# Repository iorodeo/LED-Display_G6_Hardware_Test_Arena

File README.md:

## LED-Display\_G6\_Hardware\_Test\_Arena

This repository is part of <https://reiserlab.github.io/Modular-LED-Display/>.
It contains the KiCad design and production files for the G6 panel test arena
hardware.

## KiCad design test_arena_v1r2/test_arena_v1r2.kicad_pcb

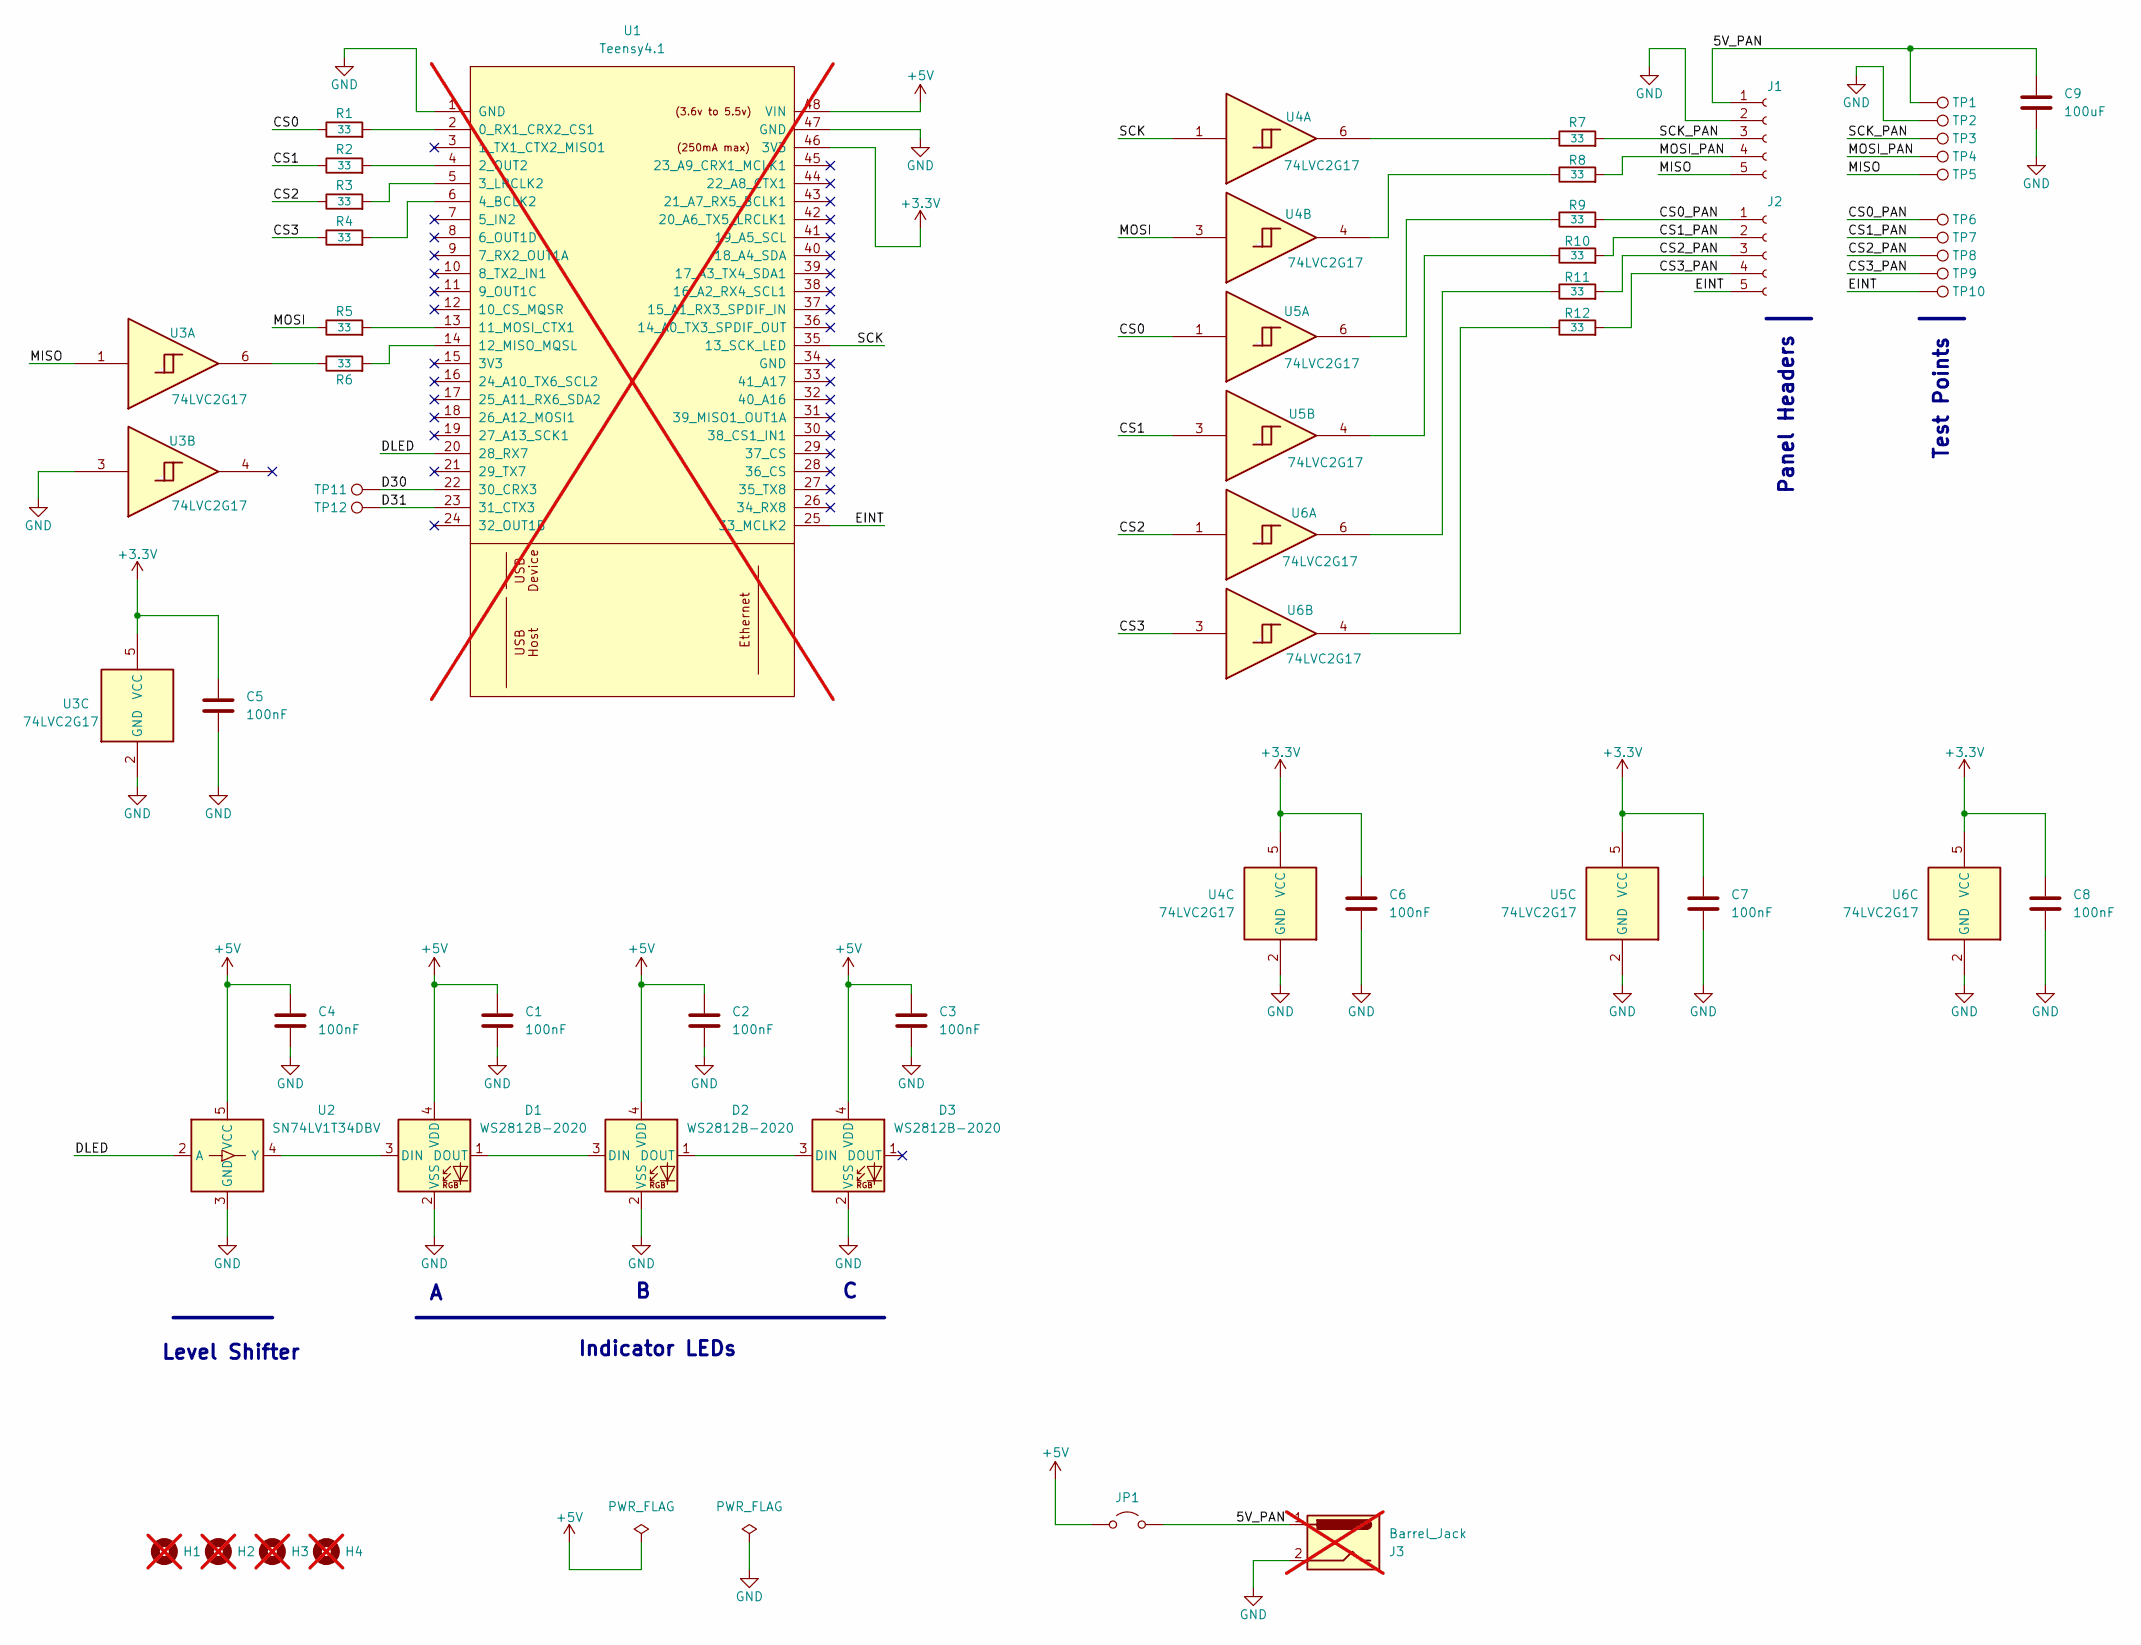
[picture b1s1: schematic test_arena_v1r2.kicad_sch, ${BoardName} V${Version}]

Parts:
C1, C2, C3, C4, C5, C6, C7, C8: 100nF; C_0402_1005Metric; LCSC Part # C1525
C9: 100uF; C_1210_3225Metric; LCSC Part # C84455
D1, D2, D3: WS2812B-2020; LED_WS2812B-2020_PLCC4_2.0x2.0mm; LCSC Part # C965555
H1, H2, H3, H4: MountingHole; MountingHole_3.2mm_M3; not fitted
J1, J2: Conn_01x05_Socket; PinSocket_1x05_P2.54mm_Vertical; LCSC Part # C50950
J3: Barrel_Jack; DCJACK_2PIN_HIGHCURRENT; not fitted
JP1: Jumper_2_Open; PinHeader_1x02_P2.54mm_Vertical; LCSC Part # C492401
R1, R2, R3, R4, R5, R6, R7, R8, R9, R10, R11, R12: 33; R_0402_1005Metric; LCSC Part # C25105
TP1, TP2, TP3, TP4, TP5, TP6, TP7, TP8, TP9, TP10, TP11, TP12: TestPoint; TestPoint_THTPad_D2.0mm_Drill1.0mm; LCSC Part # C238122
U1: Teensy4.1; Teensy41_outer_only; not fitted
U2: SN74LV1T34DBV; SOT-23-5; LCSC Part # C100024
U3, U4, U5, U6: 74LVC2G17; SOT-23-6; LCSC Part # C10429

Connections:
+3.3V: C5.1, C6.1, C7.1, C8.1, U1.46 (3V3), U3.5 (VCC), U4.5 (VCC), U5.5 (VCC), U6.5 (VCC)
+5V: C1.1, C2.1, C3.1, C4.1, D1.4 (VDD), D2.4 (VDD), D3.4 (VDD), JP1.1 (A), U1.48 (VIN), U2.5 (VCC)
/5V_PAN: C9.1, J1.1, J3.1, JP1.2 (B), TP1.1
/CS0: R1.1, U5.1
/CS0_PAN: J2.1, R9.2, TP6.1
/CS1: R2.1, U5.3
/CS1_PAN: J2.2, R10.2, TP7.1
/CS2: R3.1, U6.1
/CS2_PAN: J2.3, R11.2, TP8.1
/CS3: R4.1, U6.3
/CS3_PAN: J2.4, R12.2, TP9.1
/D30: TP11.1, U1.22 (30_CRX3)
/D31: TP12.1, U1.23 (31_CTX3)
/DLED: U1.20 (28_RX7), U2.2 (A)
/EINT: J2.5, TP10.1, U1.25 (33_MCLK2)
/MISO: J1.5, TP5.1, U3.1
/MOSI: R5.1, U4.3
/MOSI_PAN: J1.4, R8.2, TP4.1
/SCK: U1.35 (13_SCK_LED), U4.1
/SCK_PAN: J1.3, R7.2, TP3.1
GND: C1.2, C2.2, C3.2, C4.2, C5.2, C6.2, C7.2, C8.2, C9.2, D1.2 (VSS), D2.2 (VSS), D3.2 (VSS), J1.2, J3.2, TP2.1, U1.1 (GND), U1.47 (GND), U2.3 (GND), U3.2 (GND), U3.3, U4.2 (GND), U5.2 (GND), U6.2 (GND)
unnamed: D1.3 (DIN), U2.4 (Y)
unnamed: D1.1 (DOUT), D2.3 (DIN)
unnamed: D2.1 (DOUT), D3.3 (DIN)
unnamed: R6.1, U3.6
unnamed: R7.1, U4.6
unnamed: R8.1, U4.4
unnamed: R9.1, U5.6
unnamed: R10.1, U5.4
unnamed: R11.1, U6.6
unnamed: R12.1, U6.4
unnamed: R1.2, U1.2 (0_RX1_CRX2_CS1)
unnamed: R2.2, U1.4 (2_OUT2)
unnamed: R3.2, U1.5 (3_LRCLK2)
unnamed: R4.2, U1.6 (4_BCLK2)
unnamed: R5.2, U1.13 (11_MOSI_CTX1)
unnamed: R6.2, U1.14 (12_MISO_MQSL)

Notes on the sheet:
Test Points
Indicator LEDs
Panel Headers
Level Shifter

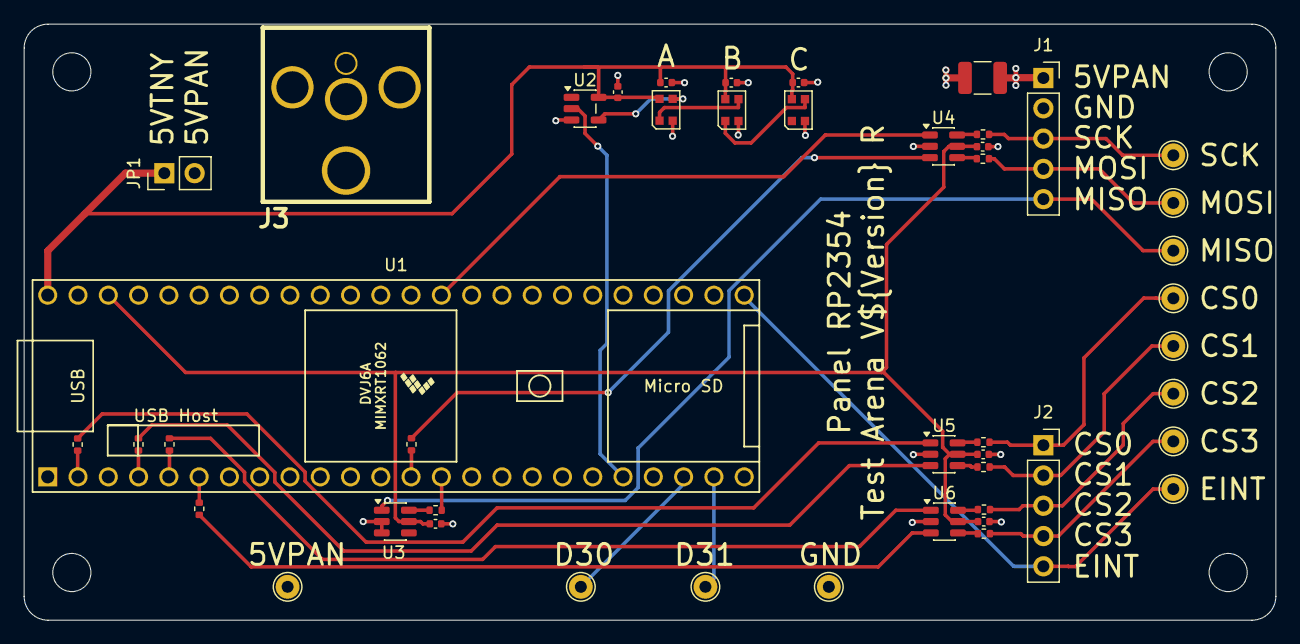
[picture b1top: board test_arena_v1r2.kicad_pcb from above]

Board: 4 copper layers, 105.0 x 50.0 mm, 50 parts (0 on the bottom side), 37 nets.

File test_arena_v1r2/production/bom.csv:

Designator,Footprint,Quantity,Value,LCSC Part #
"C1, C2, C3, C4, C5, C6, C7, C8",0402,8,100nF,C1525
C9,1210,1,100uF,C84455
"D1, D2, D3",LED_WS2812B-2020_PLCC4_2.0x2.0mm,3,WS2812B-2020,C965555
"J1, J2",PinSocket_1x05_P2.54mm_Vertical,2,Conn_01x05_Socket,C50950
JP1,PinHeader_1x02_P2.54mm_Vertical,1,Jumper_2_Open,C492401
"R1, R10, R11, R12, R2, R3, R4, R5, R6, R7, R8, R9",0402,12,33,C25105
"TP1, TP10, TP11, TP12, TP2, TP3, TP4, TP5, TP6, TP7, TP8, TP9",TestPoint_THTPad_D2.0mm_Drill1.0mm,12,TestPoint,C238122
U2,SOT-23-5,1,SN74LV1T34DBV,C100024
"U3, U4, U5, U6",SOT-23-6,4,74LVC2G17,C10429

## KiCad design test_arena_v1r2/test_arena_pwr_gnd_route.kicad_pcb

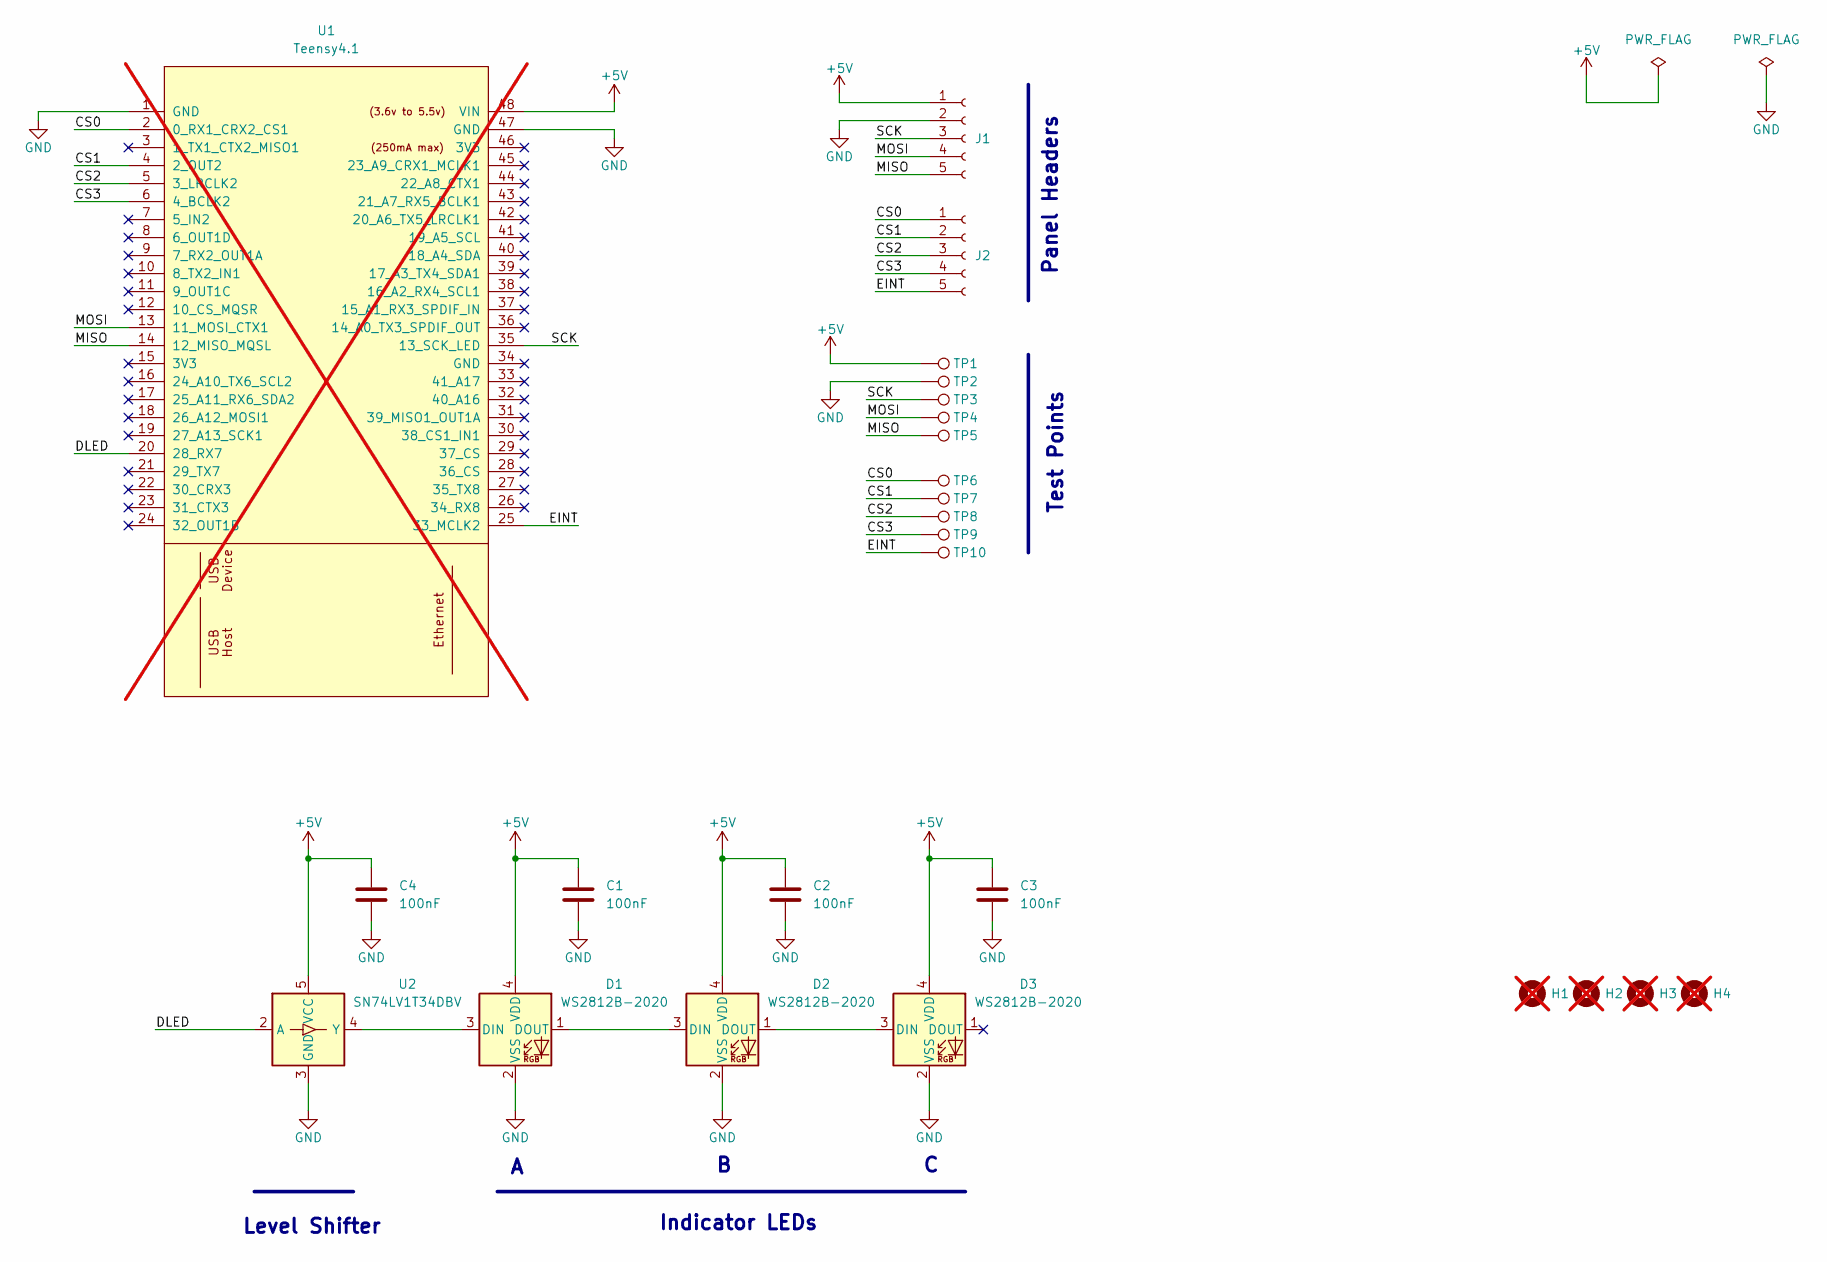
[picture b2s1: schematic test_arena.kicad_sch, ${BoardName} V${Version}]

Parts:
C1, C2, C3, C4: 100nF; C_0402_1005Metric; LCSC Part # C1525
D1, D2, D3: WS2812B-2020; LED_WS2812B-2020_PLCC4_2.0x2.0mm; LCSC Part # C965555
H1, H2, H3, H4: MountingHole; MountingHole_3.2mm_M3; not fitted
J1, J2: Conn_01x05_Socket; PinHeader_1x05_P2.54mm_Vertical; LCSC Part # C50950
TP1, TP2, TP3, TP4, TP5, TP6, TP7, TP8, TP9, TP10: TestPoint; TestPoint_THTPad_D2.0mm_Drill1.0mm; LCSC Part # C238122
U1: Teensy4.1; Teensy41_outer_only; not fitted
U2: SN74LV1T34DBV; SOT-23-5; LCSC Part # C100024

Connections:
+5V: C1.1, C2.1, C3.1, C4.1, D1.4 (VDD), D2.4 (VDD), D3.4 (VDD), J1.1, TP1.1, U1.48 (VIN), U2.5 (VCC)
/CS0: J2.1, TP6.1, U1.2 (0_RX1_CRX2_CS1)
/CS1: J2.2, TP7.1, U1.4 (2_OUT2)
/CS2: J2.3, TP8.1, U1.5 (3_LRCLK2)
/CS3: J2.4, TP9.1, U1.6 (4_BCLK2)
/DLED: U1.20 (28_RX7), U2.2 (A)
/EINT: J2.5, TP10.1, U1.25 (33_MCLK2)
/MISO: J1.5, TP5.1, U1.14 (12_MISO_MQSL)
/MOSI: J1.4, TP4.1, U1.13 (11_MOSI_CTX1)
/SCK: J1.3, TP3.1, U1.35 (13_SCK_LED)
GND: C1.2, C2.2, C3.2, C4.2, D1.2 (VSS), D2.2 (VSS), D3.2 (VSS), J1.2, TP2.1, U1.1 (GND), U1.47 (GND), U2.3 (GND)
unnamed: D1.3 (DIN), U2.4 (Y)
unnamed: D1.1 (DOUT), D2.3 (DIN)
unnamed: D2.1 (DOUT), D3.3 (DIN)

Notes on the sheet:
Test Points
Indicator LEDs
Panel Headers
Level Shifter

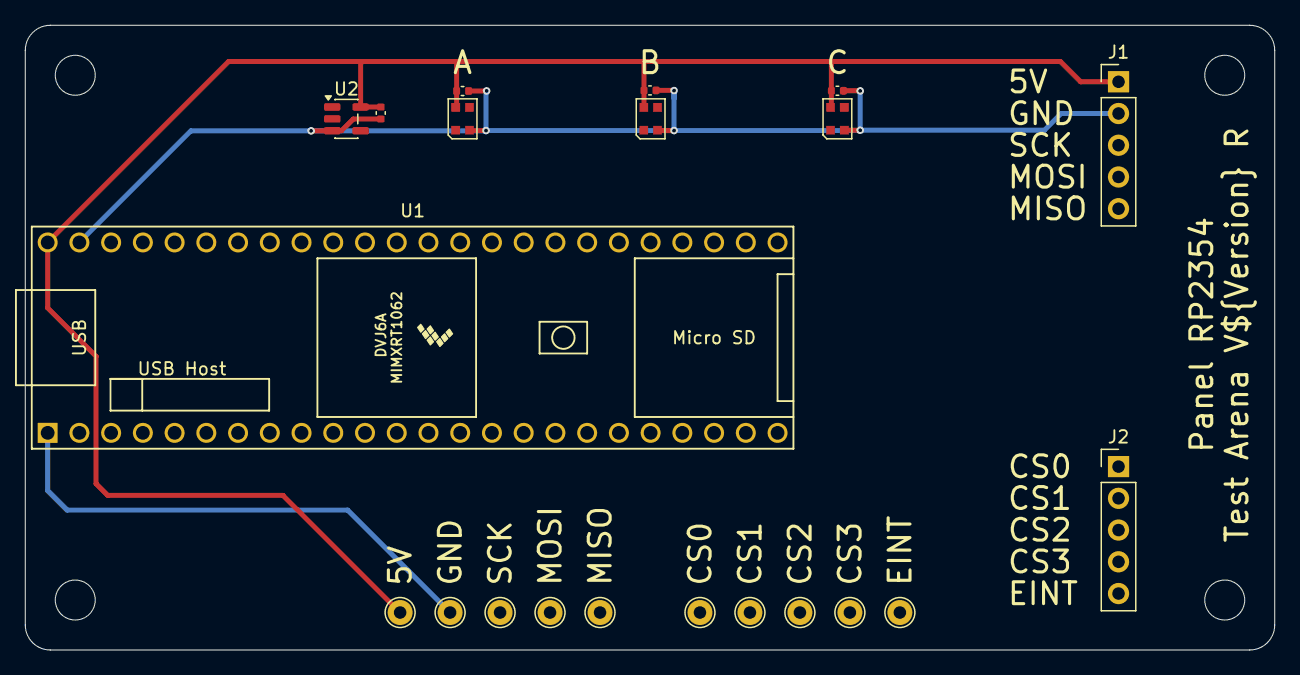
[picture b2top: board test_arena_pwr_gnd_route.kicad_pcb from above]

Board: 2 copper layers, 100.0 x 50.0 mm, 25 parts (0 on the bottom side), 14 nets.

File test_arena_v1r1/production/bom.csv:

Designator,Footprint,Quantity,Value,LCSC Part #
"C1, C2, C3, C4",0402,4,100nF,C1525
"D1, D2, D3",LED_WS2812B-2020_PLCC4_2.0x2.0mm,3,WS2812B-2020,C965555
"J1, J2",PinHeader_1x05_P2.54mm_Vertical,2,Conn_01x05_Socket,C50950
"TP1, TP10, TP2, TP3, TP4, TP5, TP6, TP7, TP8, TP9",TestPoint_THTPad_D2.0mm_Drill1.0mm,10,TestPoint,C238122
U2,SOT-23-5,1,SN74LV1T34DBV,C100024

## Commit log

2025-11-25 Project creation.
2025-11-25 Added production archive.
2025-12-17 Added modified V0.1 R1 test arena design.
    This design incorporates the same SPI signal handling as is
    planned for the 10-ring arena.
2025-12-18 Added final design for modified test arena.
2025-12-31 Added production files for v1r2 test arena.
2026-01-19 Fixed wrong part issue on v1r2 test arena.
2026-04-27 documentation for website
